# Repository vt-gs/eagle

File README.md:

# eagle --OBSOLETE--
EagleCAD schematics, boards, and libraries

## --OBSOLETE--

The projects in this repository have been moved to their own stand alone repositories.  Finally decided it was dumb to have everything in one repo, because if anyone else actually wants to use one thing, they would have to clone everything.

The files in this repo will no longer be updated and new projects will be created in their own repo.  This repo is not being nuked for the moment and is being kept around as an archival repo in case I forgot to move something over to its own repo.  Eventually, this will get nuked.

## -------------

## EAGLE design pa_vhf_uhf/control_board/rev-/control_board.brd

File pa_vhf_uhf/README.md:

# VHF/UHF Power Amplifier Control Electronics

For associated Arduino Code See this repo:

https://github.com/vt-gs/pa_vhf_uhf

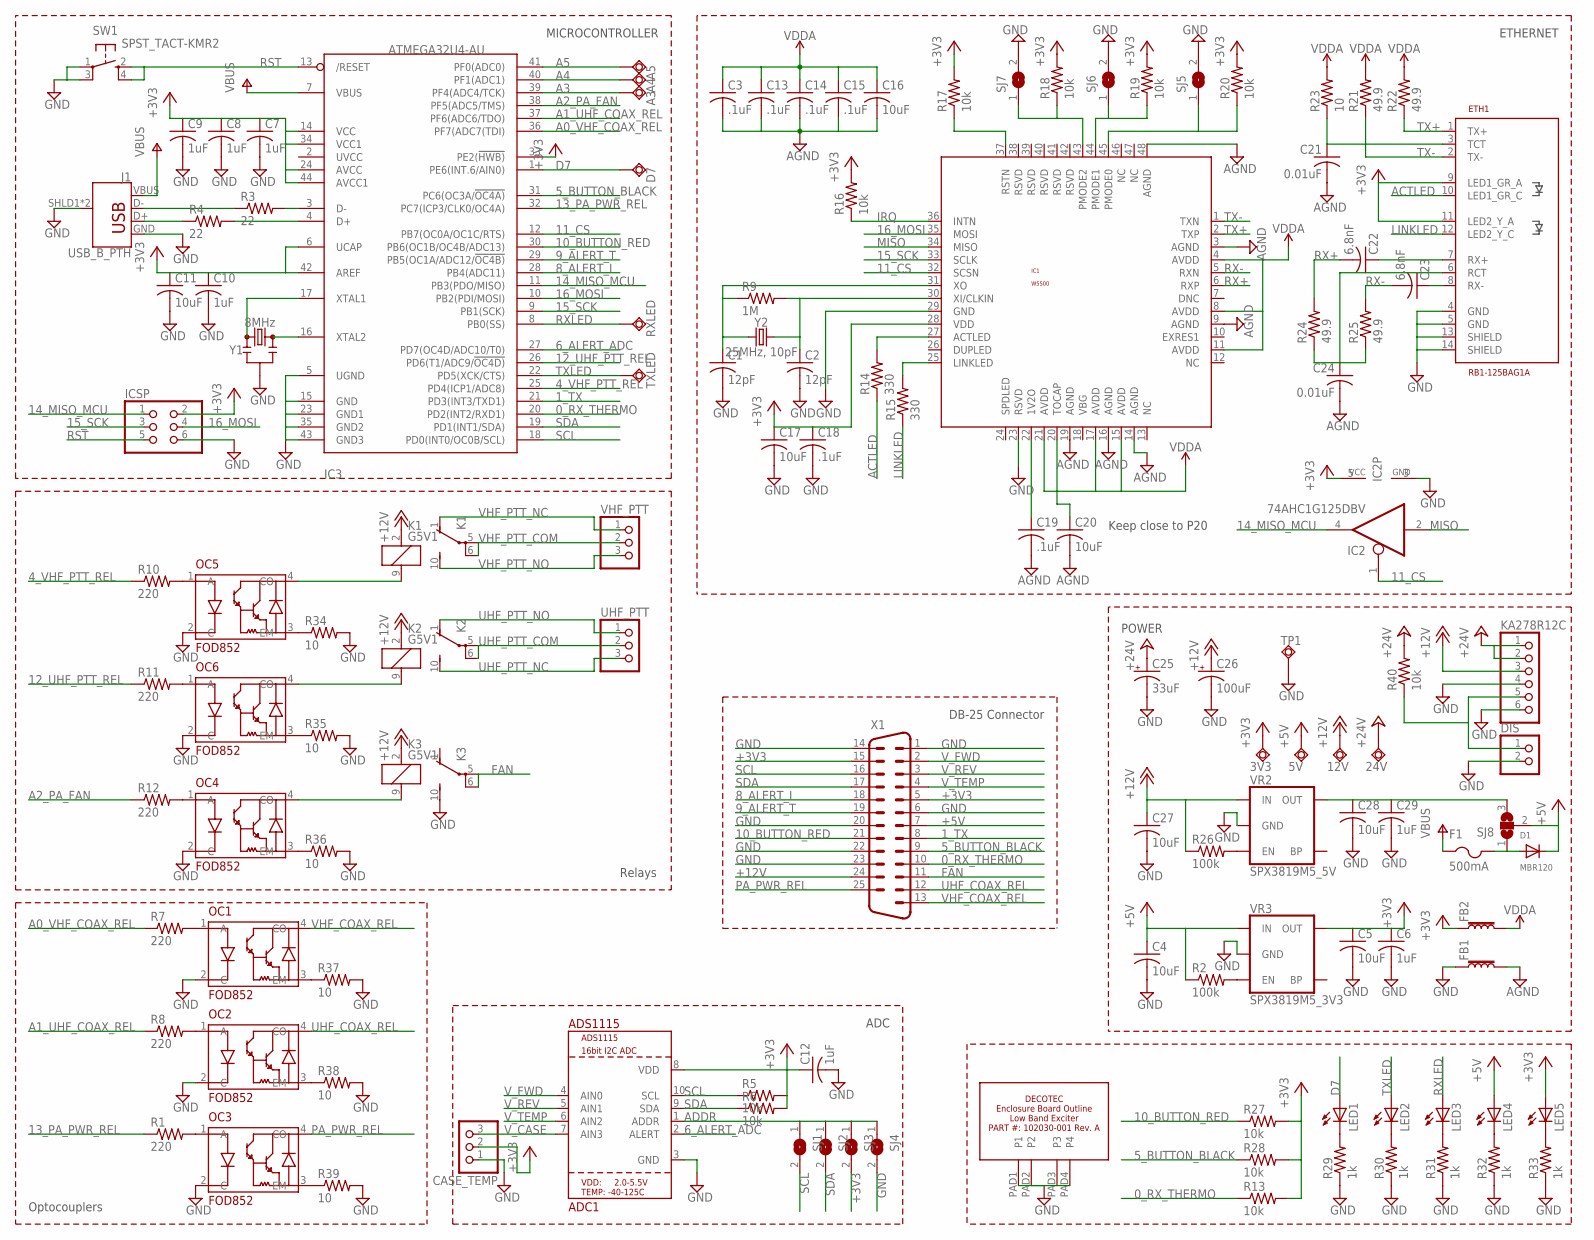
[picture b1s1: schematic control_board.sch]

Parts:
3V3, 5V, 12V, 24V: TPSQTP20SQ; TP20SQ
A3, A4, A5: TPSQTP20SQ; TP20SQ
ADC1: ADS1115; MSOP10
C1, C2: 12pF; C0805K
C3, C13, C14, C15, C18, C19: .1uF; C0805K
C4, C5, C11, C16, C17, C20, C27, C28: 10uF; C0805K
C6, C7, C8, C9, C10, C12, C29: 1uF; C0805K
C21, C24: 0.01uF; C0805K
C22, C23: 6.8nF; C0805K
C25: 33uF; PANASONIC_C
C26: 100uF; PANASONIC_D
CASE_TEMP: PINHD-1X3; 1X03
D1: MBR120; SOD-123
D7: TPSQTP20SQ; TP20SQ
DIS: PINHD-1X2; 1X02
ETH1: RB1-125BAG1A
F1: 500mA; R1206
FB1, FB2: FERRITE_BEAD; 0805
IC1: W5500; LQFP48
IC2: 74AHC1G125DBV; SOT23-5
IC3: ATMEGA32U4-AU; TQFP44
ICSP: PINHD-2X3; 2X03
J1: USB_B_PTH; USB-B-PTH
K1, K2, K3: G5V1
KA278R12C: PINHD-1X6; 1X06
LED1, LED2, LED3, LED4, LED5: LEDCHIPLED_0805; CHIPLED_0805
OC1, OC2, OC3, OC4, OC5, OC6: FOD852; SMD4-7
R1, R7, R8, R10, R11, R12: 220; R0805
R2, R26: 100k; R0805
R3, R4: 22; R0805
R5, R6, R13, R16, R17, R18, R19, R20, R27, R28, R40: 10k; R0805
R9: 1M; R0805
R14, R15: 330; R0805
R21, R22, R24, R25: 49.9; R0805
R23, R34, R35, R36, R37, R38, R39: 10; R0805
R29, R30, R31, R32, R33: 1k; R0805
RXLED: TPSQTP20SQ; TP20SQ
SJ1, SJ2, SJ3, SJ4, SJ5, SJ6, SJ7: SJ
SJ8: SJ2W; SJ_2
SW1: SPST_TACT-KMR2; KMR2
TP1: TPSQTP20SQ; TP20SQ
TXLED: TPSQTP20SQ; TP20SQ
U$3: DECOTEC_102030-001AV3; DECOTEC_102030-001A_V3
UHF_PTT: PINHD-1X3; 1X03
VHF_PTT: PINHD-1X3; 1X03
VR2: SPX3819M5_5V; SOT23-5
VR3: SPX3819M5_3V3; SOT23-5
X1: DB25_MALEVB; M25VB
Y1: 8MHz; RESONATOR-SMD-3.2X1.3
Y2: 25MHz, 10pF; CRYSTAL-SMD-3.2X2.5MM

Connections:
0_RX_THERMO: IC3.20 (PD2(INT2/RXD1)), R13.1, X1.10
1_TX: IC3.21 (PD3(INT3/TXD1)), X1.8
4_VHF_PTT_REL: IC3.25 (PD4(ICP1/ADC8)), R10.1
5_BUTTON_BLACK: IC3.31 (PC6(OC3A/!OC4A)), R28.1, X1.9
6_ALERT_ADC: ADC1.2 (ALERT), IC3.27 (PD7(OC4D/ADC10/T0))
8_ALERT_I: IC3.28 (PB4(ADC11)), X1.18
9_ALERT_T: IC3.29 (PB5(OC1A/ADC12/!OC4B)), X1.19
10_BUTTON_RED: IC3.30 (PB6(OC1B/OC4B/ADC13)), R27.1, X1.21
11_CS: IC1.32 (SCSN), IC2.1 (OE), IC3.12 (PB7(OC0A/OC1C/RTS))
12_UHF_PTT_REL: IC3.26 (PD6(T1/ADC9/!OC4D)), R11.1
13_PA_PWR_REL: IC3.32 (PC7(ICP3/CLK0/OC4A)), R1.1
14_MISO_MCU: IC2.4 (O), IC3.11 (PB3(PDO/MISO)), ICSP.1
15_SCK: IC1.33 (SCLK), IC3.9 (PB1(SCK)), ICSP.3
16_MOSI: IC1.35 (MOSI), IC3.10 (PB2(PDI/MOSI)), ICSP.4
+3V3: 3V3.TP, ADC1.8 (VDD), C5.1, C6.1, C7.1, C8.1, C9.1, C10.1, C11.1, C12.1, C17.1, C18.1, CASE_TEMP.2, ETH1.9 (LED1_GR_A), ETH1.11 (LED2_Y_A), FB2.1, IC1.28 (VDD), IC2.5 (VCC), IC3.6 (UCAP), IC3.14 (VCC), IC3.24 (AVCC), IC3.33 (PE2(!HWB)), IC3.34 (VCC1), IC3.42 (AREF), IC3.44 (AVCC1), ICSP.2, LED5.A, R5.2, R6.2, R13.2, R16.2, R17.2, R18.2, R19.2, R20.2, R27.2, R28.2, SJ3.2, VR3.5 (OUT), X1.5, X1.15
+5V: 5V.TP, C4.1, D1.C, LED4.A, R2.1, SJ8.2, VR3.1 (IN), X1.7
+12V: 12V.TP, C26.+, C27.1, K1.2 (1), K2.2 (1), K3.2 (1), KA278R12C.3, R26.1, VR2.1 (IN), X1.24
+24V: 24V.TP, C25.+, KA278R12C.1, KA278R12C.2, R40.2
A0_VHF_COAX_REL: IC3.36 (PF7(ADC7(TDI)), R7.1
A1_UHF_COAX_REL: IC3.37 (PF6(ADC6/TDO)), R8.1
A2_PA_FAN: IC3.38 (PF5(ADC5/TMS)), R12.1
A3: A3.TP, IC3.39 (PF4(ADC4/TCK))
A4: A4.TP, IC3.40 (PF1(ADC1))
A5: A5.TP, IC3.41 (PF0(ADC0))
ACTLED: ETH1.10 (LED1_GR_C), R14.1
ADDR: ADC1.1 (ADDR), SJ1.1, SJ2.1, SJ3.1, SJ4.1
AGND: C3.2, C13.2, C14.2, C15.2, C16.2, C19.2, C20.2, C21.2, C24.2, FB1.2, IC1.3 (AGND), IC1.9 (AGND), IC1.14 (AGND), IC1.16 (AGND), IC1.19 (AGND), IC1.48 (AGND)
D7: D7.TP, IC3.1 (PE6(INT.6/AIN0)), LED1.A
FAN: K3.5, K3.6, X1.11
GND: ADC1.3 (GND), C1.2, C2.2, C4.2, C5.2, C6.2, C7.2, C8.2, C9.2, C10.2, C11.2, C12.2, C17.2, C18.2, C25.-, C26.-, C27.2, C28.2, C29.2, CASE_TEMP.1, DIS.2, ETH1.4 (GND), ETH1.5 (GND), ETH1.13 (SHIELD), ETH1.14 (SHIELD), FB1.1, IC1.23 (RSVD), IC1.29 (GND), IC2.3 (GND), IC3.5 (UGND), IC3.15 (GND), IC3.23 (GND1), IC3.35 (GND2), IC3.43 (GND3), ICSP.6, J1.GND, J1.SHLD1 (SHIELD), J1.SHLD2 (SHIELD), K3.10 (S), KA278R12C.4, KA278R12C.6, OC1.2 (C), OC2.2 (C), OC3.2 (C), OC4.2 (C), OC5.2 (C), OC6.2 (C), R29.1, R30.1, R31.1, R32.1, R33.1, R34.2, R35.2, R36.2, R37.2, R38.2, R39.2, SJ4.2, SJ5.2, SJ6.2, SJ7.2, SW1.1, SW1.3 (P1), TP1.TP, U$3.PAD1 (P1), U$3.PAD2 (P2), U$3.PAD3 (P3), U$3.PAD4 (P4), VR2.2 (GND), VR3.2 (GND), X1.1, X1.6, X1.14, X1.20, X1.22, X1.23, Y1.2
IRQ: IC1.36 (INTN), R16.1
LINKLED: ETH1.12 (LED2_Y_C), R15.1
MISO: IC1.34 (MISO), IC2.2 (I)
unnamed: OC3.1 (A), R1.2
unnamed: K3.9 (2), OC4.4 (CO)
unnamed: R2.2, VR3.3 (EN)
unnamed: IC3.17 (XTAL1), Y1.1
unnamed: IC3.16 (XTAL2), Y1.3
unnamed: C1.1, IC1.31 (XO), R9.1, Y2.1
unnamed: C2.1, IC1.30 (XI/CLKIN), R9.2, Y2.3 (2)
unnamed: J1.D-, R3.1
unnamed: IC3.3 (D-), R3.2
unnamed: IC3.4 (D+), R4.2
unnamed: J1.D+, R4.1
unnamed: OC1.1 (A), R7.2
unnamed: OC2.1 (A), R8.2
unnamed: IC1.37 (RSTN), R17.1
unnamed: OC5.1 (A), R10.2
unnamed: LED1.C, R29.2
unnamed: LED2.C, R30.2
unnamed: LED4.C, R32.2
unnamed: LED5.C, R33.2
unnamed: OC6.1 (A), R11.2
unnamed: OC4.1 (A), R12.2
unnamed: K1.9 (2), OC5.4 (CO)
unnamed: K2.9 (2), OC6.4 (CO)
unnamed: LED3.C, R31.2
unnamed: OC5.3 (EM), R34.1
unnamed: OC6.3 (EM), R35.1
unnamed: OC4.3 (EM), R36.1
unnamed: OC1.3 (EM), R37.1
unnamed: IC1.27 (ACTLED), R14.2
unnamed: IC1.25 (LINKLED), R15.2
unnamed: C28.1, C29.1, SJ8.3, VR2.5 (OUT)
unnamed: OC2.3 (EM), R38.1
unnamed: C20.1, IC1.20 (TOCAP)
unnamed: C19.1, IC1.22 (1V2O)
unnamed: C23.1, ETH1.8 (RX-)
unnamed: C22.1, ETH1.7 (RX+)
unnamed: C24.1, ETH1.6 (RCT), R24.1, R25.1
unnamed: R26.2, VR2.3 (EN)
unnamed: D1.A, F1.2, SJ8.1
unnamed: OC3.3 (EM), R39.1
unnamed: DIS.1, KA278R12C.5, R40.1
PA_PWR_REL: OC3.4 (CO), X1.25
PMODE0: IC1.45 (PMODE0), R20.1, SJ5.1
PMODE1: IC1.44 (PMODE1), R19.1, SJ6.1
PMODE2: IC1.43 (PMODE2), R18.1, SJ7.1
RST: IC3.13 (/RESET), ICSP.5, SW1.2 (S), SW1.4 (S1)
RX+: C22.2, IC1.6 (RXP), R24.2
RX-: C23.2, IC1.5 (RXN), R25.2
RXLED: IC3.8 (PB0(SS)), LED3.A, RXLED.TP
SCL: ADC1.10 (SCL), IC3.18 (PD0(INT0/OC0B/SCL)), R5.1, SJ1.2, X1.16
SDA: ADC1.9 (SDA), IC3.19 (PD1(INT1/SDA)), R6.1, SJ2.2, X1.17
TCT: C21.1, ETH1.3 (TCT), R23.1
TX+: ETH1.1 (TX+), IC1.2 (TXP), R22.1
TX-: ETH1.2 (TX-), IC1.1 (TXN), R21.1
TXLED: IC3.22 (PD5(XCK/CTS)), LED2.A, TXLED.TP
UHF_COAX_REL: OC2.4 (CO), X1.12
UHF_PTT_COM: K2.5, K2.6, UHF_PTT.2
UHF_PTT_NC: K2.10 (S), UHF_PTT.3
UHF_PTT_NO: K2.1 (O), UHF_PTT.1
VBUS: F1.1, IC3.7 (VBUS), J1.VBUS
VDDA: C3.1, C13.1, C14.1, C15.1, C16.1, FB2.2, IC1.4 (AVDD), IC1.8 (AVDD), IC1.11 (AVDD), IC1.15 (AVDD), IC1.17 (AVDD), IC1.21 (AVDD), R21.2, R22.2, R23.2
VHF_COAX_REL: OC1.4 (CO), X1.13
VHF_PTT_COM: K1.5, K1.6, VHF_PTT.2
VHF_PTT_NC: K1.1 (O), VHF_PTT.1
VHF_PTT_NO: K1.10 (S), VHF_PTT.3
V_CASE: ADC1.7 (AIN3), CASE_TEMP.3
V_FWD: ADC1.4 (AIN0), X1.2
V_REV: ADC1.5 (AIN1), X1.3
V_TEMP: ADC1.6 (AIN2), X1.4

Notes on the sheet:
Keep close to P20
ETHERNET
MICROCONTROLLER
Optocouplers
DB-25 Connector
Relays
ADC
POWER

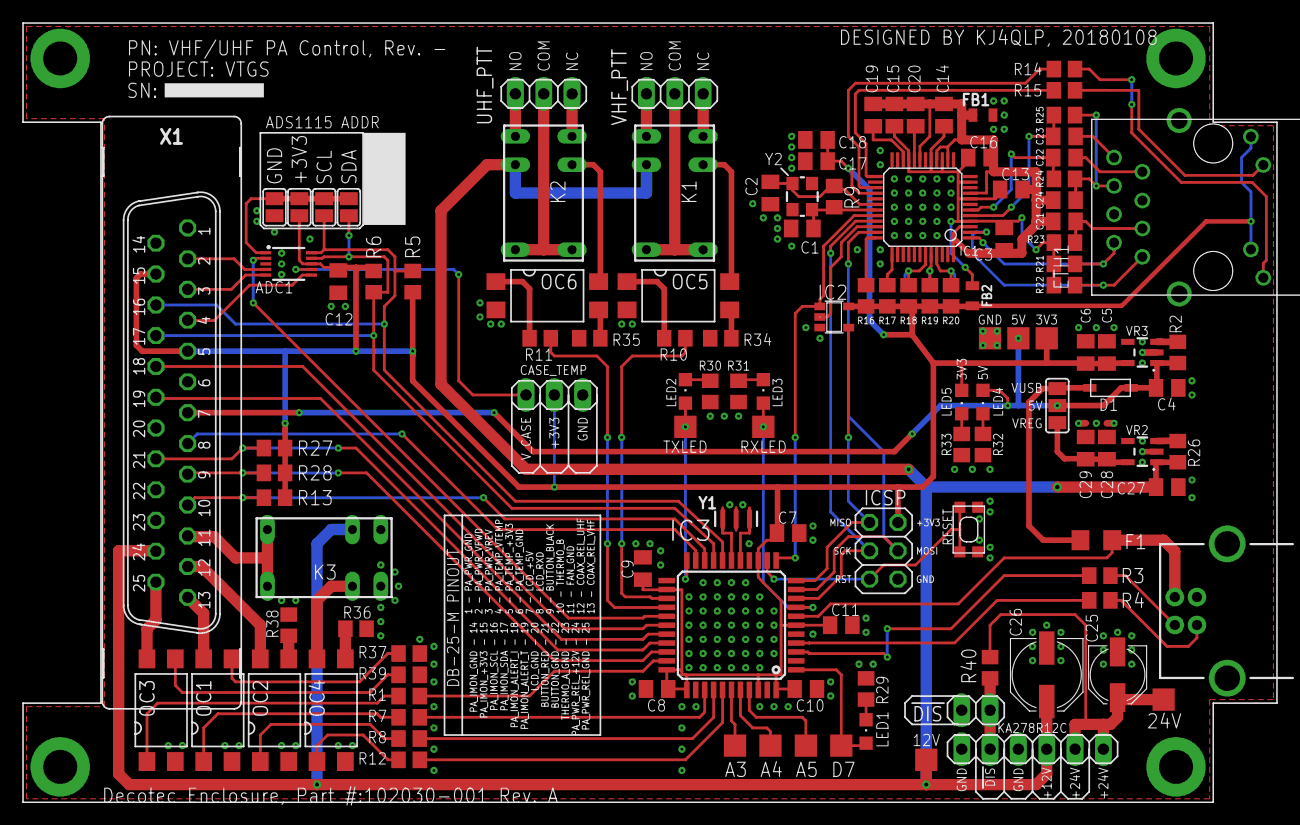
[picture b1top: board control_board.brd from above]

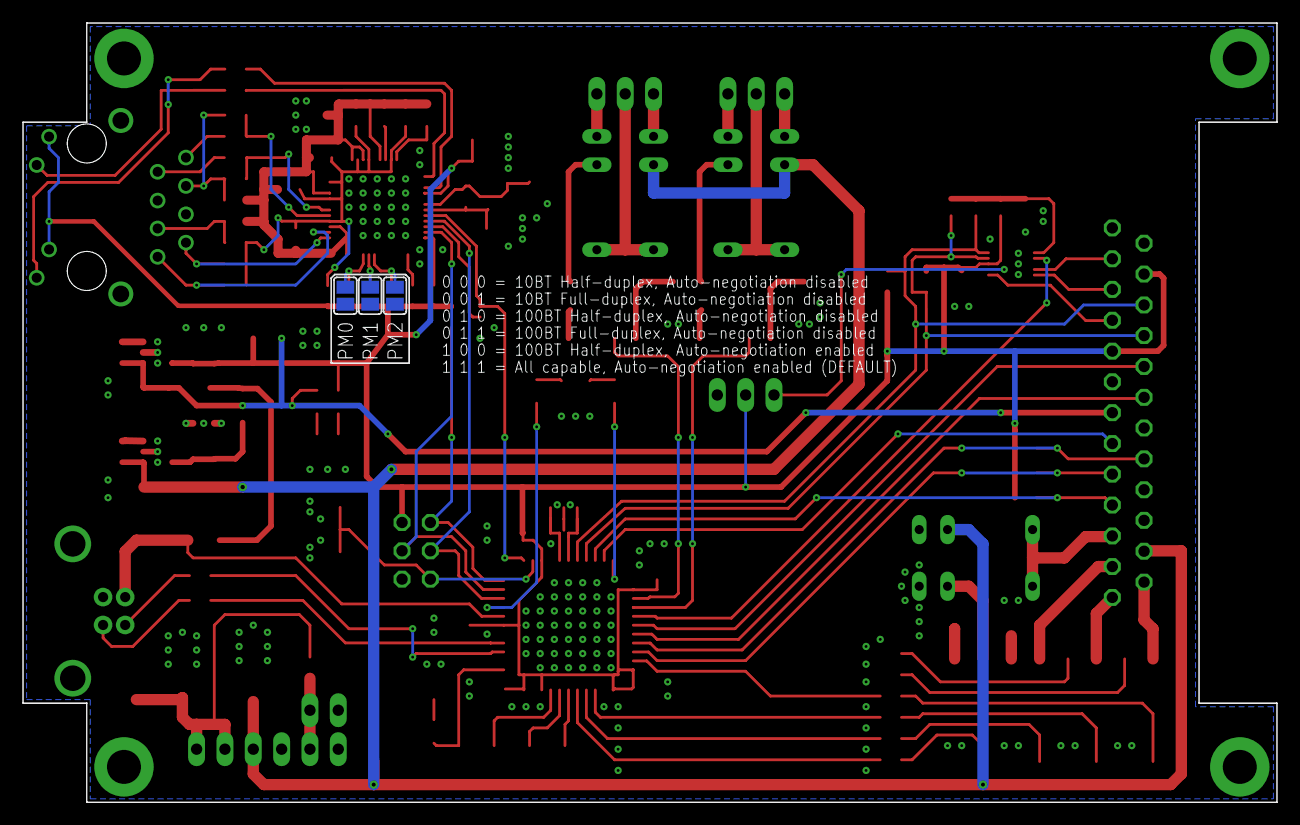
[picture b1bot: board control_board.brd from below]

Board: 2 copper layers, 112.4 x 69.8 mm, 125 parts (3 on the bottom side), 102 nets.

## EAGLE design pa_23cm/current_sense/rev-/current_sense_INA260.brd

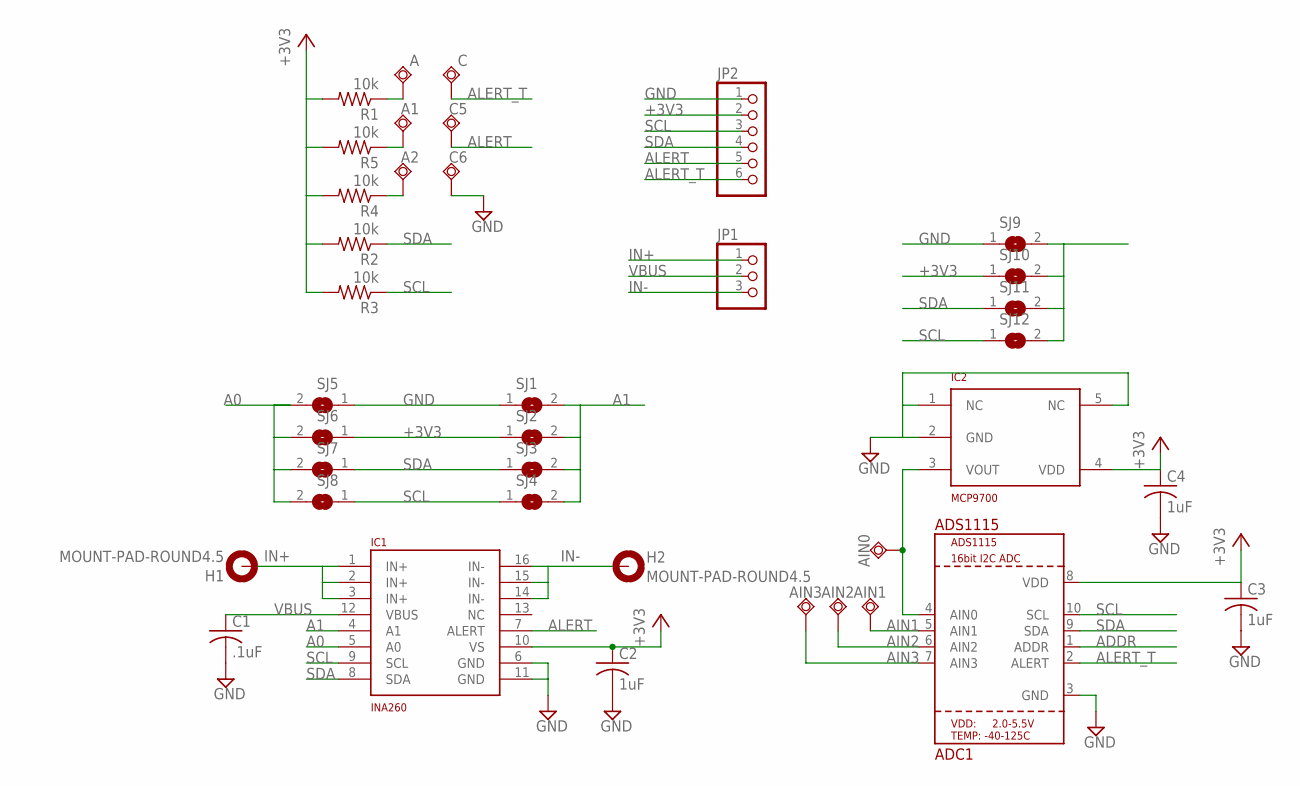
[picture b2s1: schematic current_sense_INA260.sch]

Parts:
A, A1, A2: TPSQTP20SQ; TP20SQ
ADC1: ADS1115; MSOP10
AIN0, AIN1, AIN2, AIN3: TPSQTP20SQ; TP20SQ
C: C; TP20SQ
C1: .1uF; C0805K
C2, C3, C4: 1uF; C0805K
C5, C6: TPSQTP20SQ; TP20SQ
H1, H2: MOUNT-PAD-ROUND4.5; 4,5-PAD
IC1: INA260; TSSOP16
IC2: MCP9700; SC70
JP1: PINHD-1X3; 1X03
JP2: PINHD-1X6; 1X06
R1, R2, R3, R4, R5: 10k; R0805
SJ1, SJ2, SJ3, SJ4, SJ5, SJ6, SJ7, SJ8, SJ9, SJ10, SJ11, SJ12: SJ

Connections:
+3V3: ADC1.8 (VDD), C2.1, C3.1, C4.1, IC1.10 (VS), IC2.4 (VDD), JP2.2, R1.2, R2.2, R3.2, R4.2, R5.2, SJ2.1, SJ6.1, SJ10.1
A0: IC1.5 (A0), SJ5.2, SJ6.2, SJ7.2, SJ8.2
A1: IC1.4 (A1), SJ1.2, SJ2.2, SJ3.2, SJ4.2
ADDR: ADC1.1 (ADDR), SJ9.2, SJ10.2, SJ11.2, SJ12.2
AIN1: ADC1.5 (AIN1), AIN1.TP
AIN2: ADC1.6 (AIN2), AIN2.TP
AIN3: ADC1.7 (AIN3), AIN3.TP
ALERT: C5.TP, IC1.7 (ALERT), JP2.5
ALERT_T: ADC1.2 (ALERT), C.TP, JP2.6
GND: ADC1.3 (GND), C1.2, C2.2, C3.2, C4.2, C6.TP, IC1.6 (GND), IC1.11 (GND), IC2.1 (NC), IC2.2 (GND), IC2.5 (NC), JP2.1, SJ1.1, SJ5.1, SJ9.1
IN+: H1.B4,5, IC1.1 (IN+), IC1.2 (IN+), IC1.3 (IN+), JP1.1
IN-: H2.B4,5, IC1.14 (IN-), IC1.15 (IN-), IC1.16 (IN-), JP1.3
unnamed: A2.TP, R4.1
unnamed: A1.TP, R5.1
unnamed: A.TP, R1.1
SCL: ADC1.10 (SCL), IC1.9 (SCL), JP2.3, R3.1, SJ4.1, SJ8.1, SJ12.1
SDA: ADC1.9 (SDA), IC1.8 (SDA), JP2.4, R2.1, SJ3.1, SJ7.1, SJ11.1
VBUS: C1.1, IC1.12 (VBUS), JP1.2
V_TEMP: ADC1.4 (AIN0), AIN0.TP, IC2.3 (VOUT)

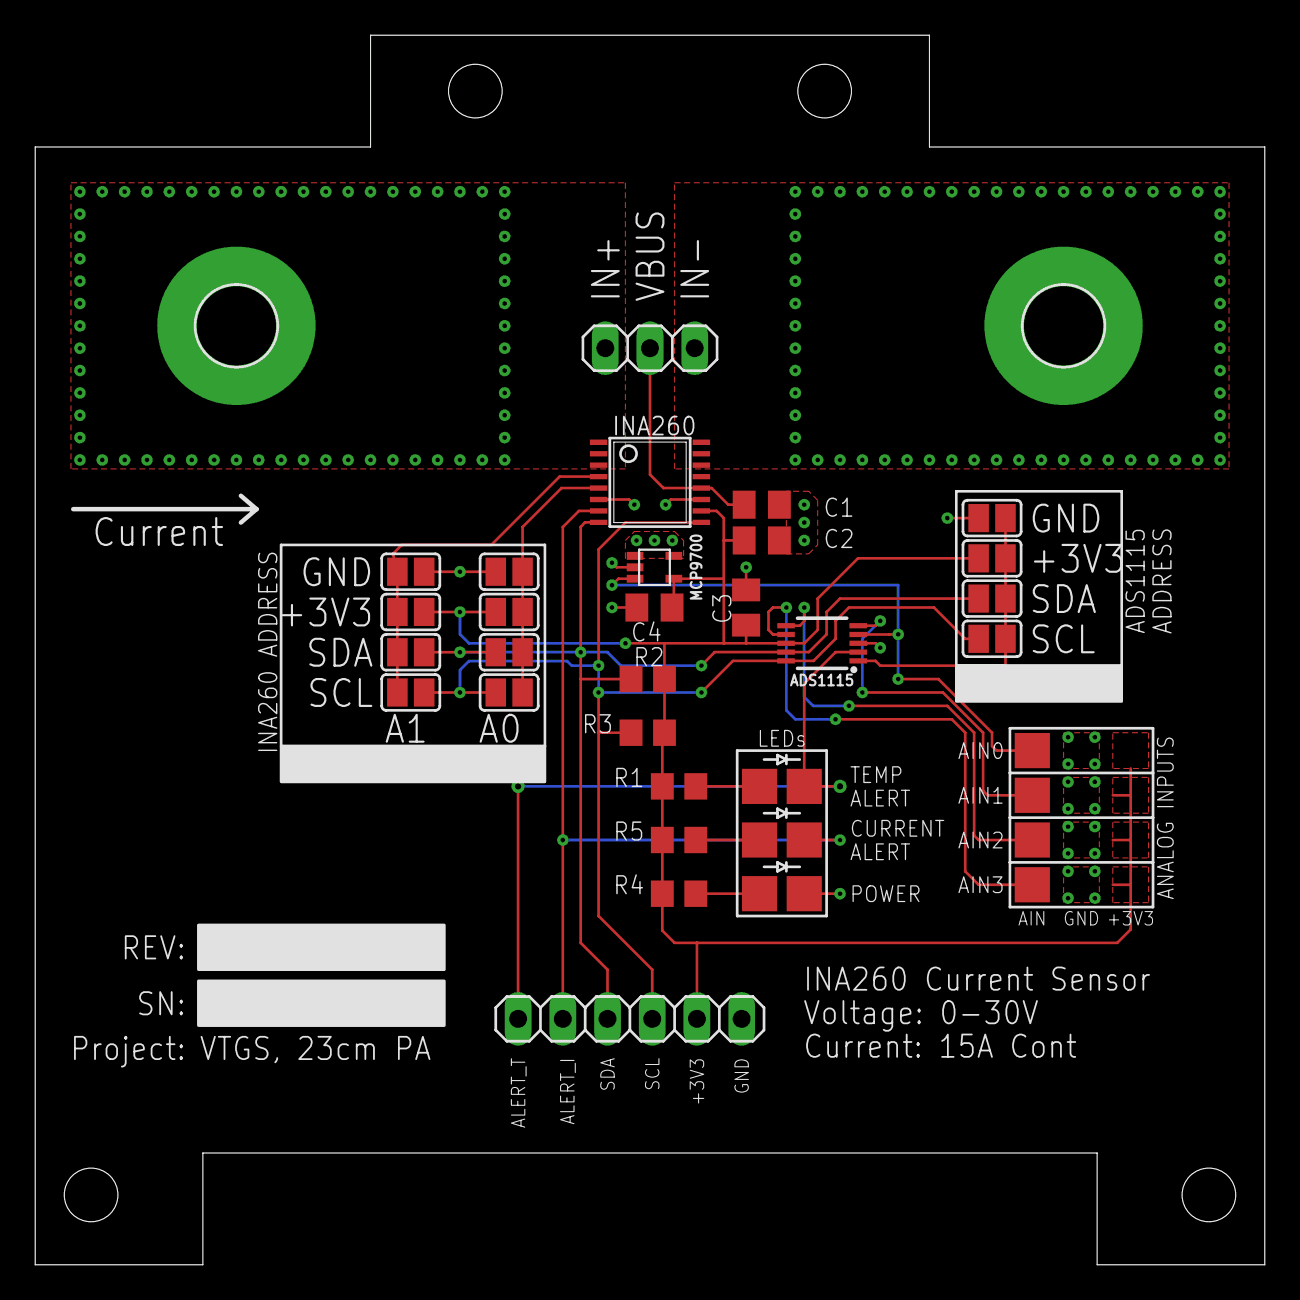
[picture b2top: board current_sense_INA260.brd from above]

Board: 2 copper layers, 69.8 x 69.8 mm, 38 parts (0 on the bottom side), 19 nets.

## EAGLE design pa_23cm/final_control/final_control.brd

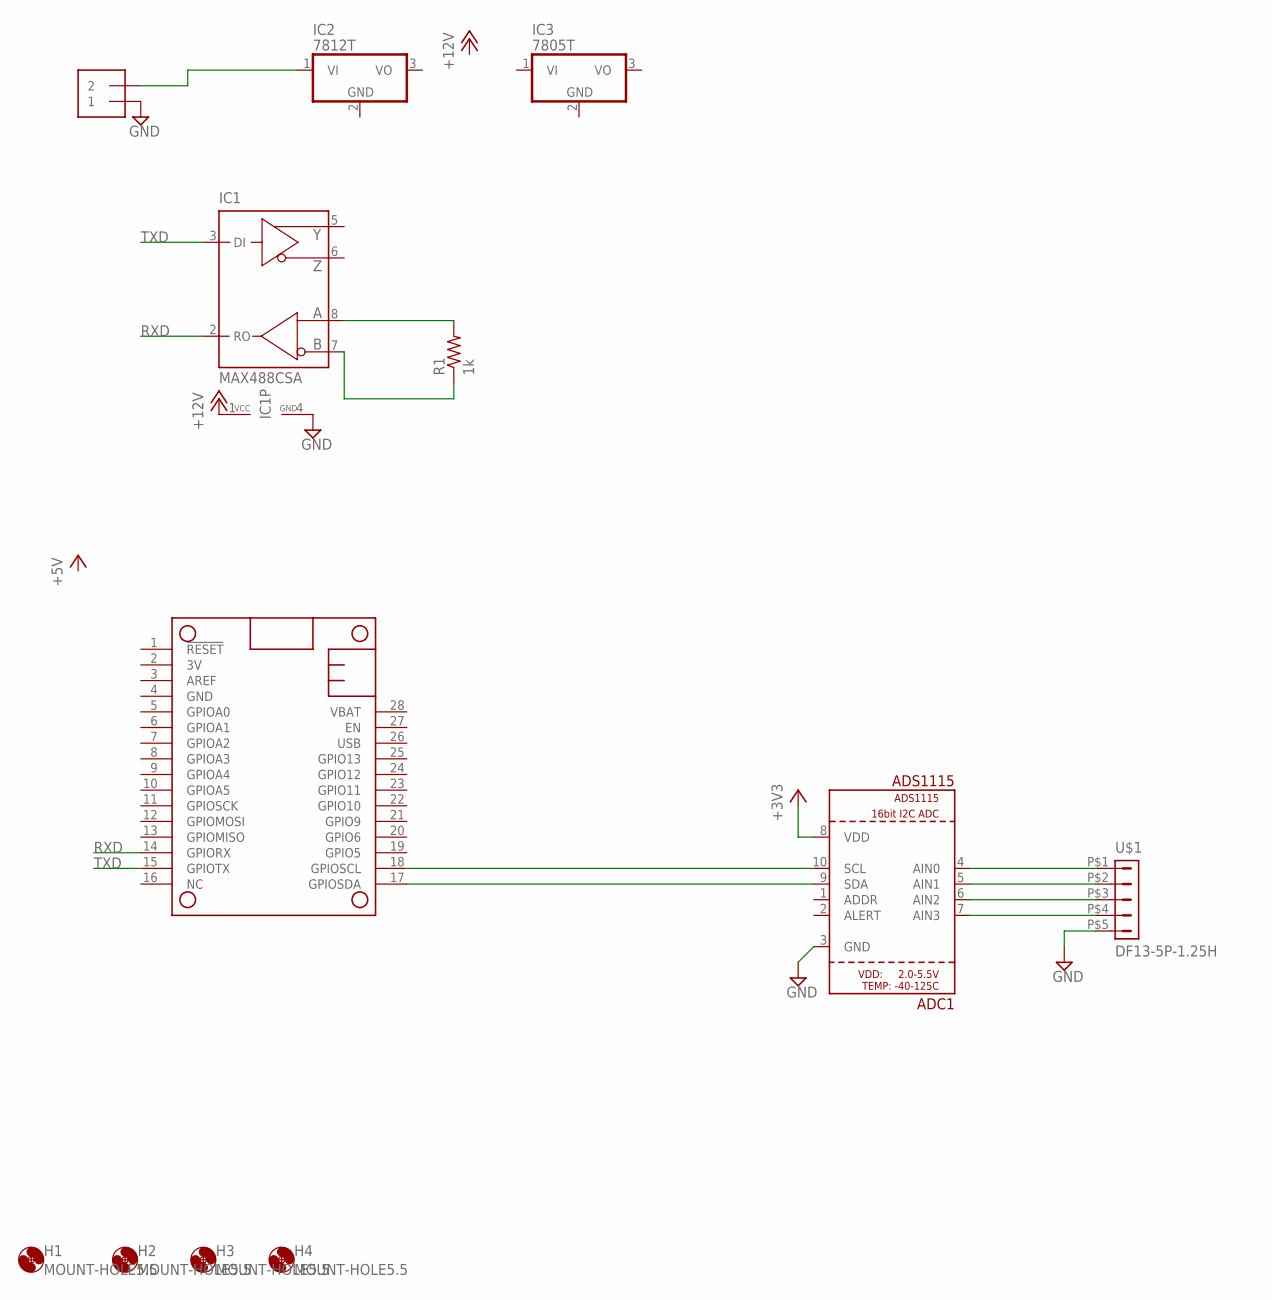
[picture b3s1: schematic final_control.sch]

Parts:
ADC1: ADS1115; MSOP10
FEATHER_32U4: FEATHERWING_NODIM; FEATHERWING_DIM
H1, H2, H3, H4: MOUNT-HOLE5.5; 5,5
IC1: MAX488CSA; SO08
IC2: 7812T; TO220H
IC3: 7805T; TO220H
J1: 1X2-3.5MM
R1: 1k; R0805
U$1: DF13-5P-1.25H; DF13A-5P-1.25H

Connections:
+3V3: ADC1.8 (VDD)
+12V: IC1.1 (VCC)
GND: ADC1.3 (GND), FEATHER_32U4.4 (GND), IC1.4 (GND), J1.1, U$1.P$5 (5)
unnamed: IC1.8 (A), R1.2
unnamed: IC1.7 (B), R1.1
unnamed: ADC1.10 (SCL), FEATHER_32U4.18 (GPIOSCL)
unnamed: ADC1.9 (SDA), FEATHER_32U4.17 (GPIOSDA)
unnamed: ADC1.4 (AIN0), U$1.P$1 (1)
unnamed: ADC1.5 (AIN1), U$1.P$2 (2)
unnamed: ADC1.6 (AIN2), U$1.P$3 (3)
unnamed: ADC1.7 (AIN3), U$1.P$4 (4)
unnamed: IC2.1 (VI), J1.2
RXD: FEATHER_32U4.14 (GPIORX), IC1.2 (RO)
TXD: FEATHER_32U4.15 (GPIOTX), IC1.3 (DI)

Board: 2 copper layers, 12 parts (0 on the bottom side), 12 nets, no tracks yet.

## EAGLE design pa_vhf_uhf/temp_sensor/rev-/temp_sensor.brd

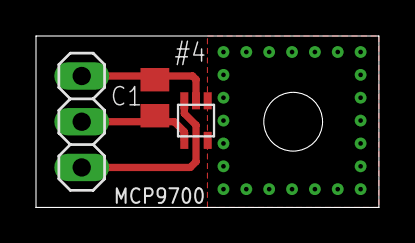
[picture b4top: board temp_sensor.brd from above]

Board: 2 copper layers, 19.1 x 9.5 mm, 3 parts (0 on the bottom side), 4 nets.

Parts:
C1: .1uF; C0805K
IC1: MCP9700; SC70
JP1: 1X03

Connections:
GND: C1.2, IC1.2, JP1.1
THERM: IC1.1, IC1.5
VDD: C1.1, IC1.4, JP1.2
VOUT: IC1.3, JP1.3

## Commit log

2017-06-19 initial commit, learning github
2017-06-19 initial commit of driver and final control board schematics and boards
2017-06-19 working on current sensor board. End of day commit.
2017-07-04 added some parts to vtgs.lbr. re-arranging sub folders for current sensor.
2017-07-04 added datasheets for current sensor.
2017-07-04 first complete version of the rev- current sensor based on INA260 chip from Texas Instruments. Design also includes a temp sensor (MCP9700) and ADS1115 ADC.
2017-07-04 staging commit for new sub folder structure for PA control boards.
2017-07-04 adding description file for VTGS EagleCAD library.
2017-07-04 added Analog Input breakout for ADS1115 ADC.
2017-07-04 added tStop layer for ADC input breakout.
2017-07-04 fixed text description on board.
2017-07-04 Adding Osh Park Top and Bottom View of board.
2017-07-11 aded DECOTEC enclosure parts to library. Updates to final control board.
2017-07-11 ading .gitignore file, currently ignores eagle CAD file extensions with '#' sign.
2017-07-12 adding datasheets for parts that were ordered for rev- model.
2017-07-12 adding current sense BOM (some extras and variants for testing).
2017-07-12 adding development kit manual/datasheet for INA260. Used as reference for schematic and layout.
2017-09-19 updated decotec 102040-002 Rev B. BNC hole spacing was incorrect.
2017-12-13 not sure what the change was...maybe to enclosures.
2017-12-13 initial commit of base files for control board and temperature sensor.
2017-12-14 final version of rev- for MCP9700 temp sensor for PA.
2017-12-14 minor updates to control board.
2017-12-14 minor tweak before sending to osh park.
2018-01-08 lots of updates, almost done, a bit more tweaking/refining of the layout. need to double check optocoupler current levels/resistors.
2018-01-11 Final Commit for Rev-. This version submitted to osh park for fab.
2018-01-28 added README with link to Arduino Code
2018-07-03 updated readme: THIS REPO IS NOW OBSOLETE
2018-07-03 updated readme, fixing typos and formatting.
2021-02-22 mass commit

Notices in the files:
parts and their libraries:
SparkFun-Connectors: Licensing: Creative Commons ShareAlike 4.0 International - https://creativecommons.org/licenses/by-sa/4.0
